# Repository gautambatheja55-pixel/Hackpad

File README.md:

# Hackpad
A custom macropad built for the Blueprint Hack Club. <br>
It includes three mechanical keys (Ctrl, C, and V independently — meaning they work as dedicated keys that combine naturally, just like a real keyboard)<br>
Hold Ctrl and tap C to copy, hold Ctrl and tap V to paste, or use Ctrl alone for any other combination.
<br>
A rotary encoder doubles as a scroll wheel for smooth document and page navigation, with its built-in push button functioning as a left click — making it a complete navigation control in one compact knob.
<br>
An RGB LED provides intuitive visual feedback: red on power-on, orange during encoder interaction, and green when a key is pressed
<br>
The custom enclosure is designed in Onshape with mirror L-shaped key layout, keeping the form factor minimal while maintaining a clean, purposeful aesthetic. The board runs on a Seeed XIAO SAMD21 microcontroller powered via USB-C, with firmware written in CircuitPython for easy modification and extensibility.

Photo of Schematic-<br>

<br>
Photo of PCB (with an Easter Egg!) - <br>

<br>
Photo of Top case -<br>

<br>
Photo of complete enclosure along with PCB - <br>

<br><br>
Onshape Link - https://cad.onshape.com/documents/47f8368e93eaf8da6dc25993/w/31c6b6148a0a80bae448b462/e/a1663b0df239ec6de66db4a1?renderMode=0&uiState=69be299fc55ce46205b5f6af

Phot
<br>
<strong>BOM</strong>

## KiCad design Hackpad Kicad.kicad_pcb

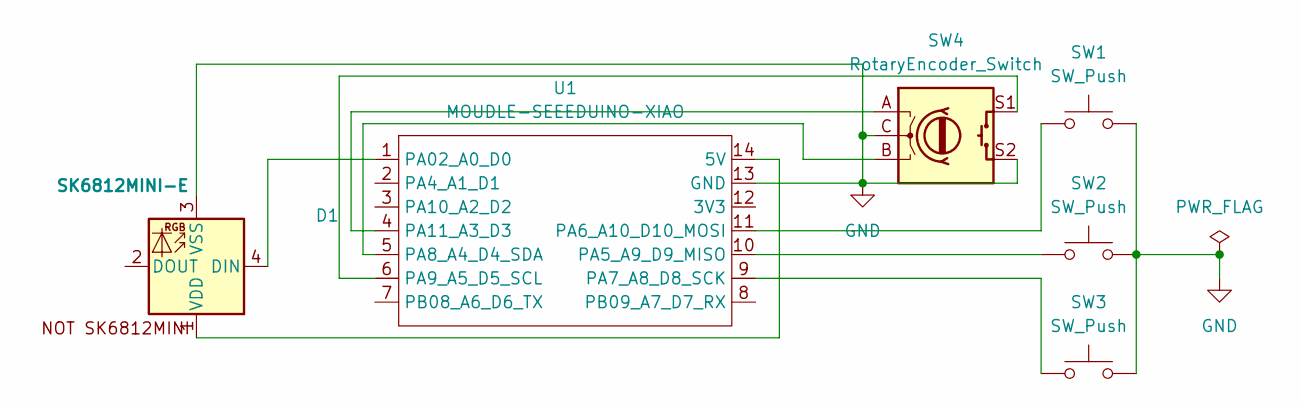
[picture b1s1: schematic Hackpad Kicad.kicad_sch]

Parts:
D1: SK6812MINI-E; SK6812MINI-E_fixed
SW1, SW2, SW3: SW_Push; SW_Cherry_MX_1.00u_PCB
SW4: RotaryEncoder_Switch; RotaryEncoder_Alps_EC11E-Switch_Vertical_H20mm
U1: MOUDLE-SEEEDUINO-XIAO; XIAO-Generic-Hybrid-14P-2.54-21X17.8MM

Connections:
GND: D1.3 (VSS), SW1.2, SW2.2, SW3.2, SW4.C, SW4.S2, U1.13 (GND)
unnamed: D1.4 (DIN), U1.1 (PA02_A0_D0)
unnamed: D1.1 (VDD), U1.14 (5V)
unnamed: SW2.1, U1.10 (PA5_A9_D9_MISO)
unnamed: SW1.1, U1.11 (PA6_A10_D10_MOSI)
unnamed: SW3.1, U1.9 (PA7_A8_D8_SCK)
unnamed: SW4.B, U1.5 (PA8_A4_D4_SDA)
unnamed: SW4.S1, U1.6 (PA9_A5_D5_SCL)
unnamed: SW4.A, U1.4 (PA11_A3_D3)

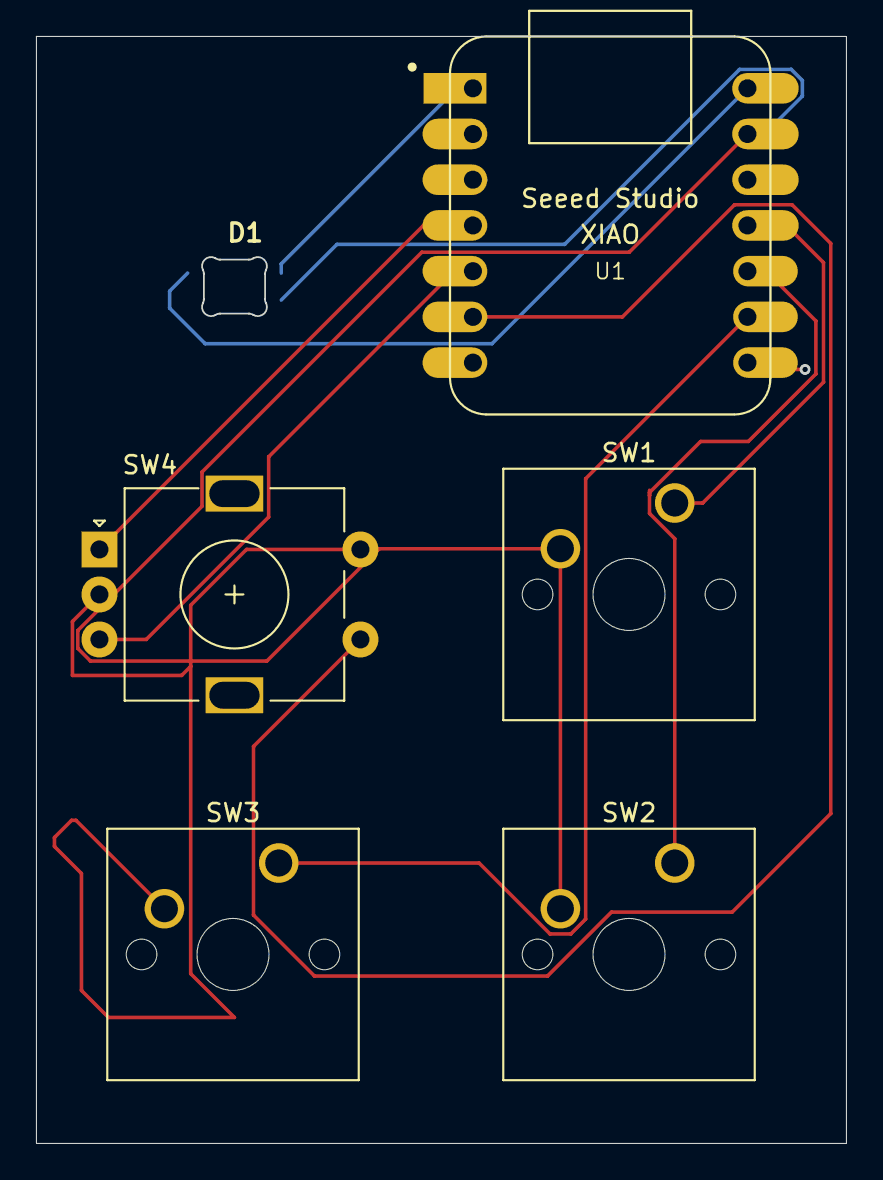
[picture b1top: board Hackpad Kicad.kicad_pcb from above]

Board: 2 copper layers, 45.0 x 61.5 mm, 6 parts (0 on the bottom side), 9 nets.

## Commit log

2026-03-19 Hardware: add KiCad pcb and schematic
2026-03-19 Rename Hackpad Kicad.kicad_pcb to hardware/Hackpad Kicad.kicad_pcb
2026-03-19 Rename Hackpad Kicad.kicad_sch to hardware/Hackpad Kicad.kicad_sch
2026-03-19 Rename Hackpad_Final_Assembly.step to CAD/Hackpad_Final_Assembly.step
2026-03-20 Rename __init__.mpy to lib/__init__.mpy
2026-03-20 Rename consumer_control.mpy to lib/consumer_control.mpy
2026-03-20 Rename keyboard.mpy to lib/keyboard.mpy
2026-03-20 Rename keycode.mpy to lib/keycode.mpy
2026-03-20 Rename consumer_control_code.mpy to lib/consumer_control_code.mpy
2026-03-20 Rename mouse.mpy to lib/mouse.mpy
2026-03-20 Rename keyboard_layout_base.mpy to lib/keyboard_layout_base.mpy
2026-03-20 Rename Hackpad.py to Code/Hackpad.py
2026-03-20 Update README.md
    Added detailed description of the custom macropad features and design.
2026-03-21 Rename Part Studio 1 (HackPad).step to CAD/Part Studio 1 (HackPad).step
2026-03-22 Rename gerbers.zip to Production/gerbers.zip
2026-03-22 Rename Part Studio 1 (HackPad).step to Part Studio 1 (HackPad).step
2026-03-22 Rename Hackpad.py to main.py
2026-03-23 Rename Top_case.step to CAD/Top_case.step
2026-03-23 Rename Bottom_case.step to CAD/Bottom_case.step
2026-03-23 Rename KiCad Pro file.zip to Hardware/KiCad Pro file.zip
